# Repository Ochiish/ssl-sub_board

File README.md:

# SubBoard for SSL

## Overview

This is a sub-board installed in the SSL robot.
The boost circuit, neopixel, phototransistor, etc. are controlled by stm32, and CAN communication is performed with the main board.

## Requirement

- KiCad 7.0.5

## Usage

Good luck...

## Features

This is a sub-board installed in an SSL robot. The board is equipped with various components such as a boost circuit, NeoPixels, phototransistors, etc., all controlled by an STM32 microcontroller. 

- This microcontroller offers advanced programming and processing capabilities, efficiently managing the robot's diverse functions.

- The boost circuit optimizes power supply, ensuring each component on the board operates at the correct voltage. It elevates the low voltage from the battery, distributing power as needed.

- NeoPixels are individually controllable LEDs used for visual feedback and status indication on the robot. These LEDs can be customized in color and brightness through programming, intuitively conveying the robot's status to the operator.

- Phototransistors detect light intensity and convert this information into digital signals. This is a crucial sensor for environmental awareness and obstacle detection in the robot.

- Furthermore, this robot is equipped with a thermistor for measuring the temperature of the solenoid coil. The thermistor plays a vital role in monitoring the heat generated by the solenoid, preventing overheating and enhancing the robot's safety and equipment lifespan.

- Additionally, the sub-board incorporates protective circuits around the power supply, safeguarding it against overvoltage and short circuits. 

- These circuits are essential for maintaining power stability while minimizing electrical risks.

- The sub-board communicates with the main board using the CAN communication protocol. CAN communication is known for its high reliability and error detection capabilities, ensuring secure data exchange between different parts of the robot. This allows for smooth overall operation and the ability to perform more complex tasks.

In this way, the sub-board supports crucial functions of the SSL robot, drawing out the robot's maximum performance through advanced technology and meticulous design.

## Reference

https://www.analog.com/media/jp/technical-documentation/data-sheets/j3751fc.pdf

## Author

[@Allsatako](http://twitter.com/Allsatako)

mail to: rionesslq@gmail.com

## Licence

There is no license as this is open source hardware.

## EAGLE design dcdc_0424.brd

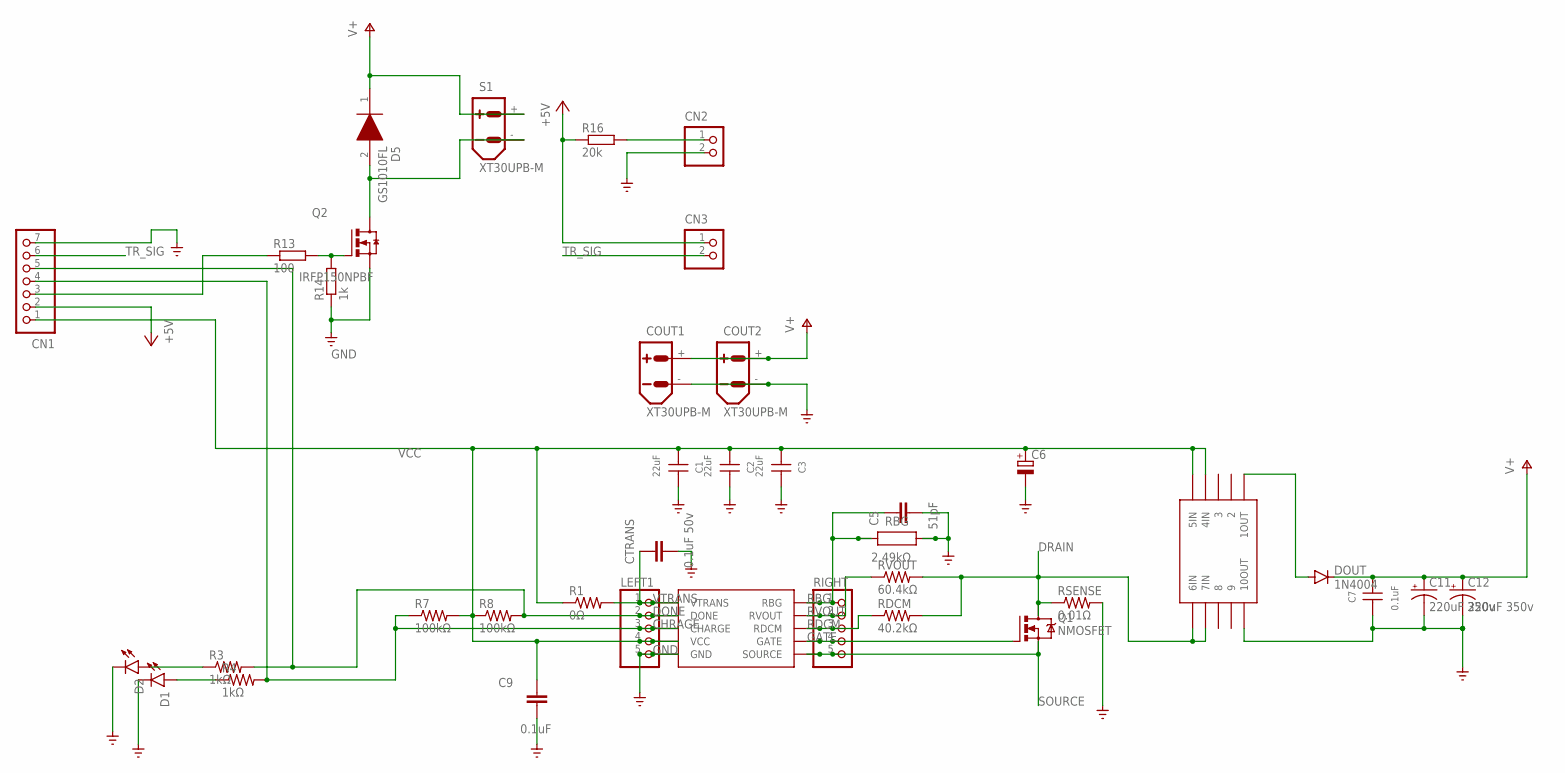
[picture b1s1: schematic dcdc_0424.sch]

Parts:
C1, C2, C3: 22uF; WCAP-CSGP_1210_H0.95
C5: 51pF; CAP_0603
C6: CPOL-EUTT2D6; TT2D6
C7: 0.1uF; WCAP-CSGP_1812_H1.25
C9: 0.1uF; CAP_0603
C11, C12: 220uF 350v; E7,5-18
CN1: B7B-XH-A
CN2, CN3: B2B-XH-A
COUT1, COUT2: XT30UPB-M
CTRANS: 0.1uF 50v; CAP_1206
D1, D2: LED_RADIALWHITE; LEDRD254W60D565H860B_W
D5: GS1010FL; SODFL3618X110N
DOUT: 1N4004; DO41-10
LEFT1: PINHD-1X5; 1X05
Q1: NMOSFET; TO220BV
Q2: IRFP150NPBF; TO-247AC
R1: 0Ω; M2012
R3, R4: 1kΩ; RES_0402
R7, R8: 100kΩ; R1210
R13: 100; R0603
R14: 1k; R0603
R16: 20k; R0603
RBG: 2.49kΩ; WRIS_PSMC_2512_6.3X3.1X0.51X1.1(LXWXHXPW)
RDCM: 40.2kΩ; RES_0805
RIGHT: PINHD-1X5; 1X05
RSENSE: 0.01Ω; RES_1206
RVOUT: 60.4kΩ; RES_0805
S1: XT30UPB-M
U$1: LT3750_2
U$2: 32052

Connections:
2: D5.2 (A), Q2.D, S1.-
+5V: CN1.2, CN3.1, R16.1
CHRAGE: CN1.4, LEFT1.3, R4.2, R7.1, U$1.CHARGE
DONE: CN1.5, LEFT1.2, R3.2, R8.2, U$1.DONE
DRAIN: Q1.D, RDCM.2, RSENSE.1, RVOUT.2, U$2.6IN, U$2.7IN
GATE: Q1.G, RIGHT.4, U$1.GATE
GND: C1.2, C2.2, C3.2, C5.2, C6.-, C7.1, C9.2, C11.-, C12.-, CN1.7, CN2.2, COUT1.-, COUT2.-, CTRANS.2, D1.C, D2.C, LEFT1.5, Q2.S, R14.1, RBG.2, RSENSE.2, U$1.GND, U$2.10OUT
unnamed: CN1.3, R13.1
unnamed: DOUT.A, U$2.1OUT
unnamed: D1.A, R4.1
unnamed: D2.A, R3.1
unnamed: Q2.G, R13.2, R14.2
unnamed: CN2.1, R16.2
RBG: C5.1, RBG.1, RIGHT.1, U$1.RBG
RDCM: RDCM.1, RIGHT.3, U$1.RDCM
RVOUT: RIGHT.2, RVOUT.1, U$1.RVOUT
SOURCE: Q1.S, RIGHT.5, U$1.SOURCE
TR_SIG: CN1.6, CN3.2
V+: C7.2, C11.+, C12.+, COUT1.+, COUT2.+, D5.1 (K), DOUT.C, S1.+
VCC: C1.1, C2.1, C3.1, C6.+, C9.1, CN1.1, LEFT1.4, R1.1, R7.2, R8.1, U$1.VCC, U$2.4IN, U$2.5IN
VTRANS: CTRANS.1, LEFT1.1, R1.2, U$1.VTRANS

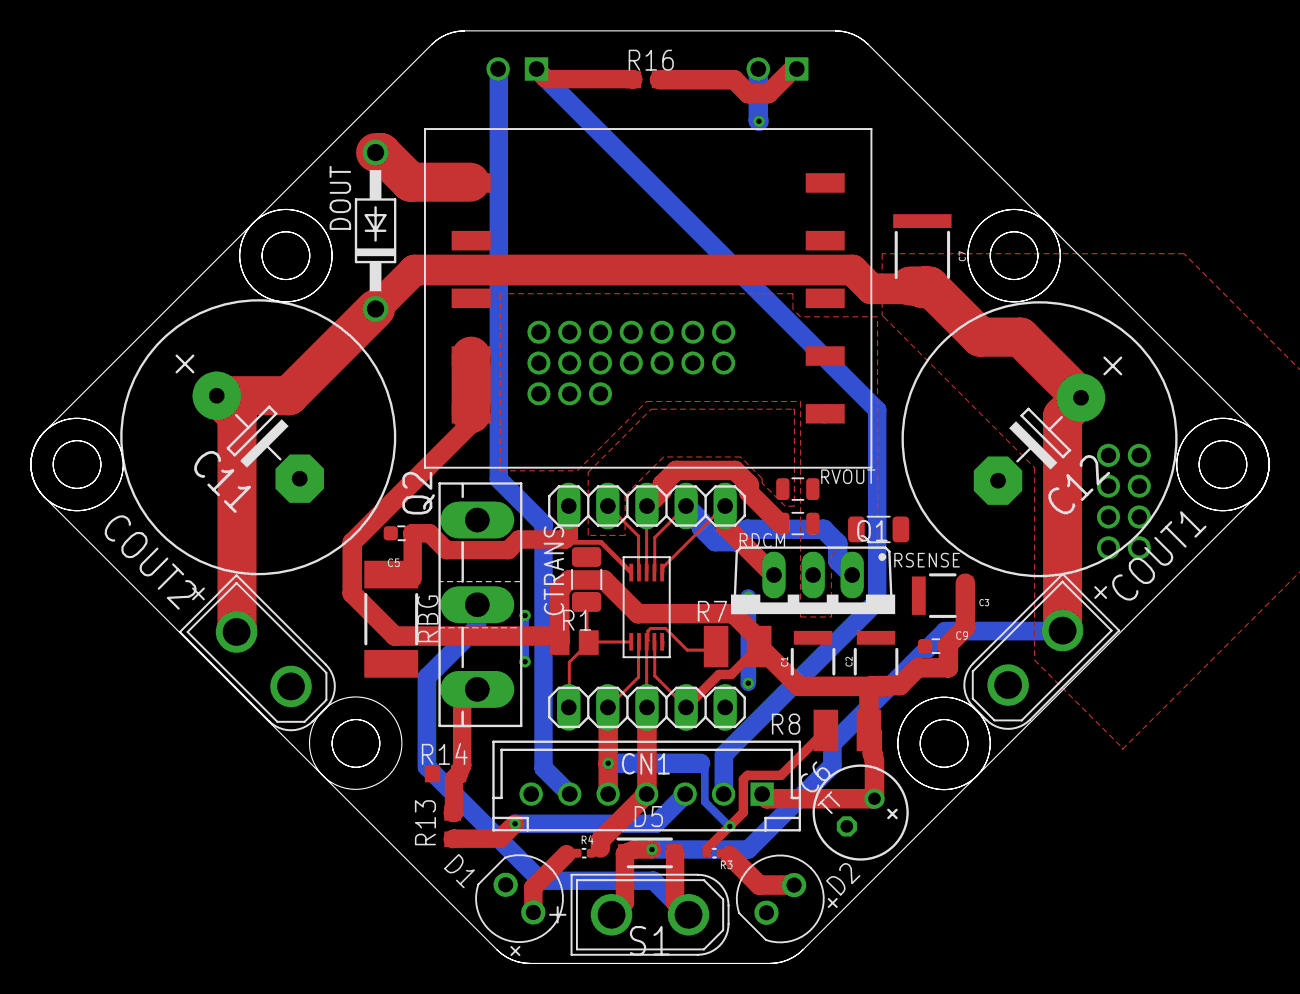
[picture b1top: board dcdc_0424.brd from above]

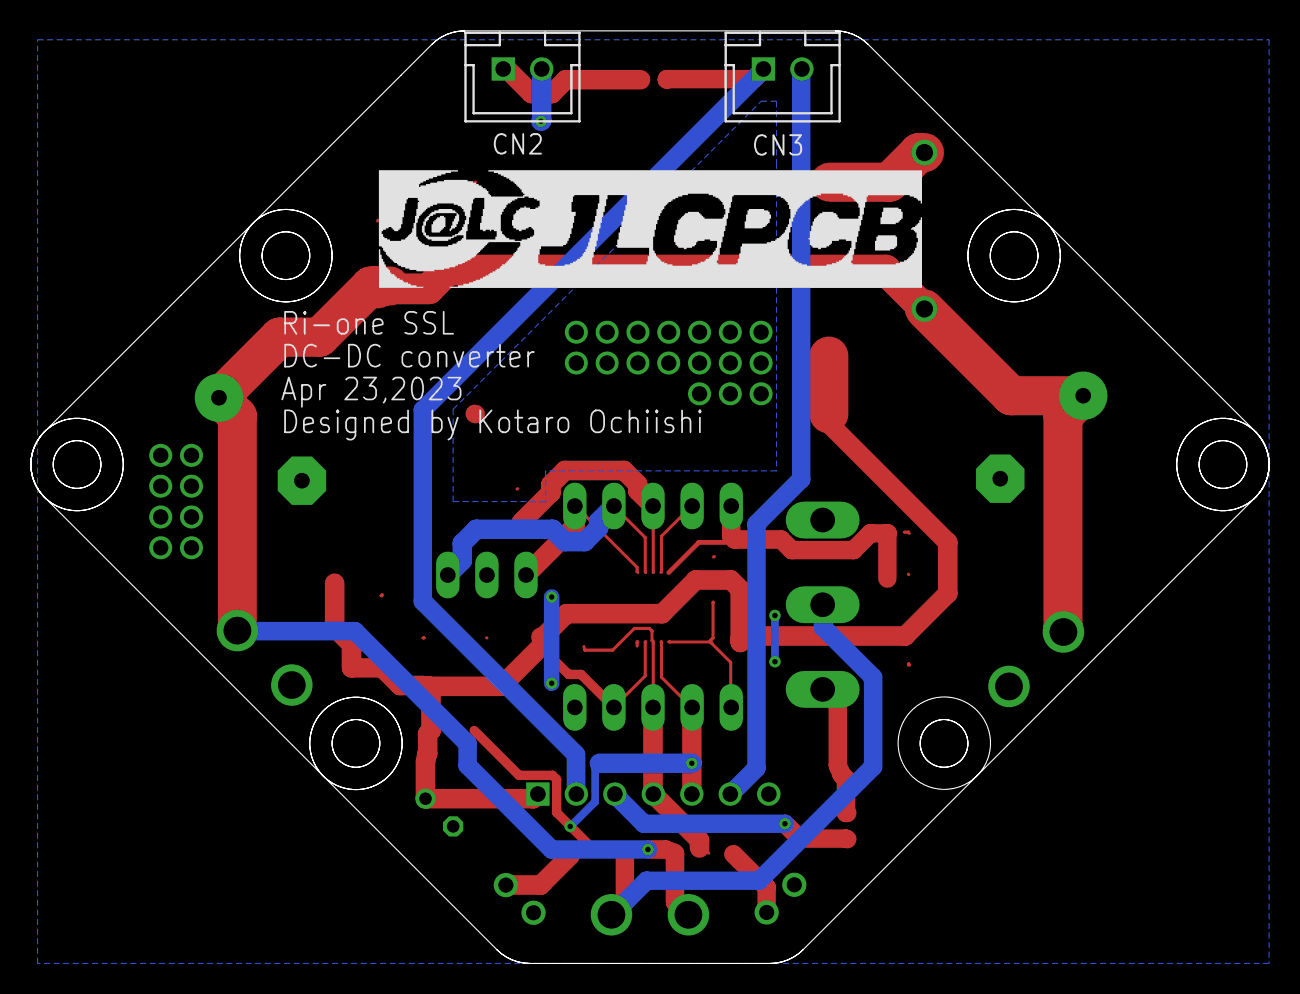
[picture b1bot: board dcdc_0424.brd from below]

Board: 2 copper layers, 80.4 x 60.6 mm, 38 parts (2 on the bottom side), 21 nets.

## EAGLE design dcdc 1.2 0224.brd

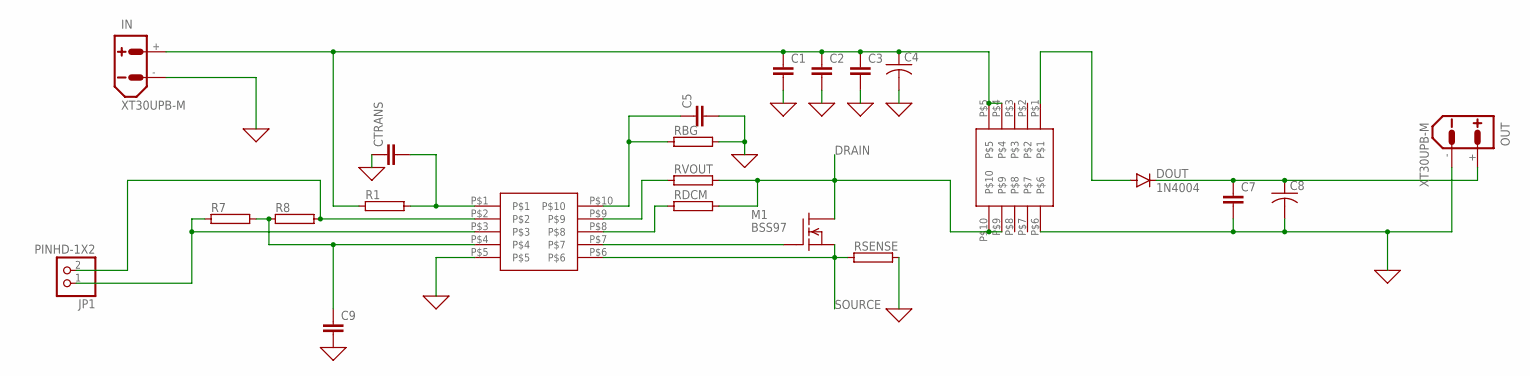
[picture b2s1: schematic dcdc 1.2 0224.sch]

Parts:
C1, C2, C3, C5, C7, C9: C5/3.5; C5B3.5
C4, C8: C-US050-050X075; C050-050X075
CTRANS: C5/3.5; C5B3.5
DOUT: 1N4004; DO41-10
IN: XT30UPB-M
JP1: PINHD-1X2; 1X02
M1: BSS97; TO202
OUT: XT30UPB-M
R1, R7, R8: RAC01; AC01
RBG: RAC01; AC01
RDCM: RAC01; AC01
RSENSE: RAC01; AC01
RVOUT: RAC01; AC01
U$1: LT3750
U$2: 32052

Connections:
0: C1.2, C2.2, C3.2, C4.2, C5.2, C7.2, C8.2, C9.2, CTRANS.1, IN.-, OUT.-, RBG.2, RSENSE.2, U$1.P$5, U$2.P$6
DRAIN: M1.2 (D), RDCM.2, RVOUT.2, U$2.P$9, U$2.P$10
unnamed: C9.1, R7.2, R8.1, U$1.P$4
unnamed: C5.1, RBG.1, U$1.P$10
unnamed: RVOUT.1, U$1.P$9
unnamed: RDCM.1, U$1.P$8
unnamed: JP1.1, R7.1, U$1.P$3
unnamed: M1.3 (G), U$1.P$7
unnamed: DOUT.A, U$2.P$1
unnamed: JP1.2, R8.2, U$1.P$2
unnamed: C7.1, C8.1, DOUT.C, OUT.+
unnamed: C1.1, C2.1, C3.1, C4.1, IN.+, R1.1, U$2.P$4, U$2.P$5
unnamed: CTRANS.2, R1.2, U$1.P$1
SOURCE: M1.1 (S), RSENSE.1, U$1.P$6

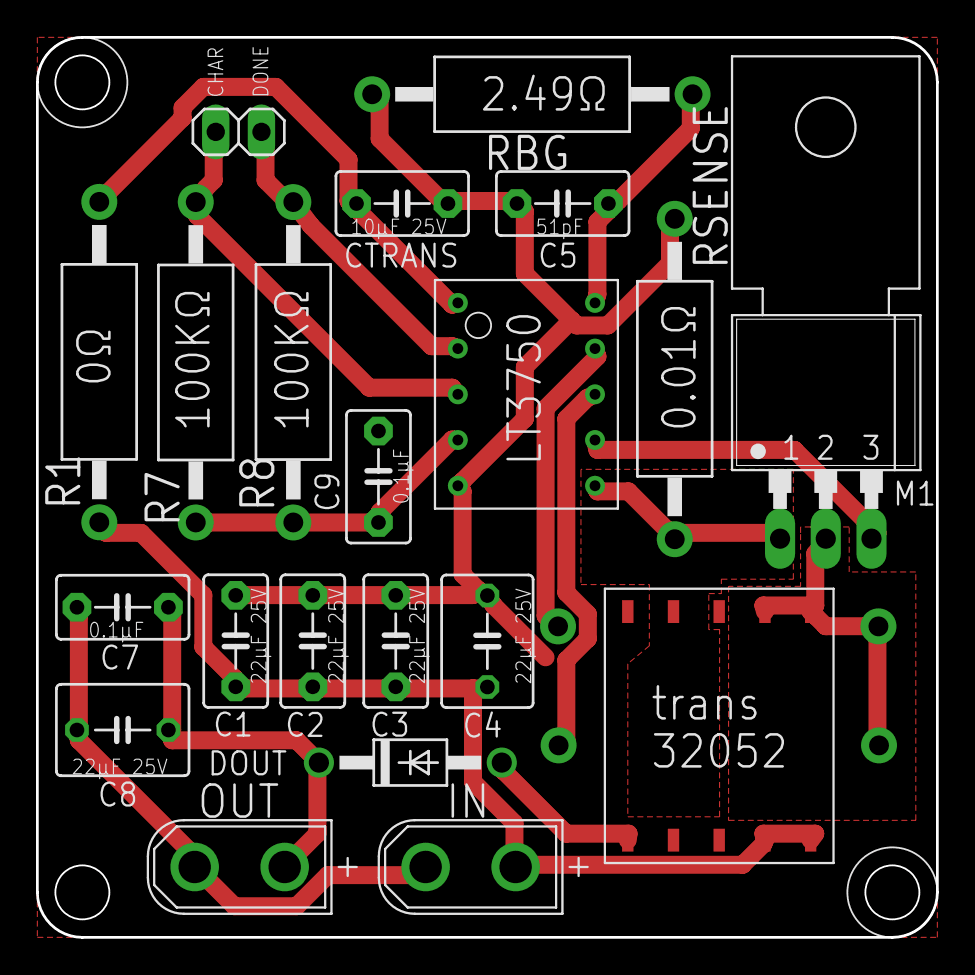
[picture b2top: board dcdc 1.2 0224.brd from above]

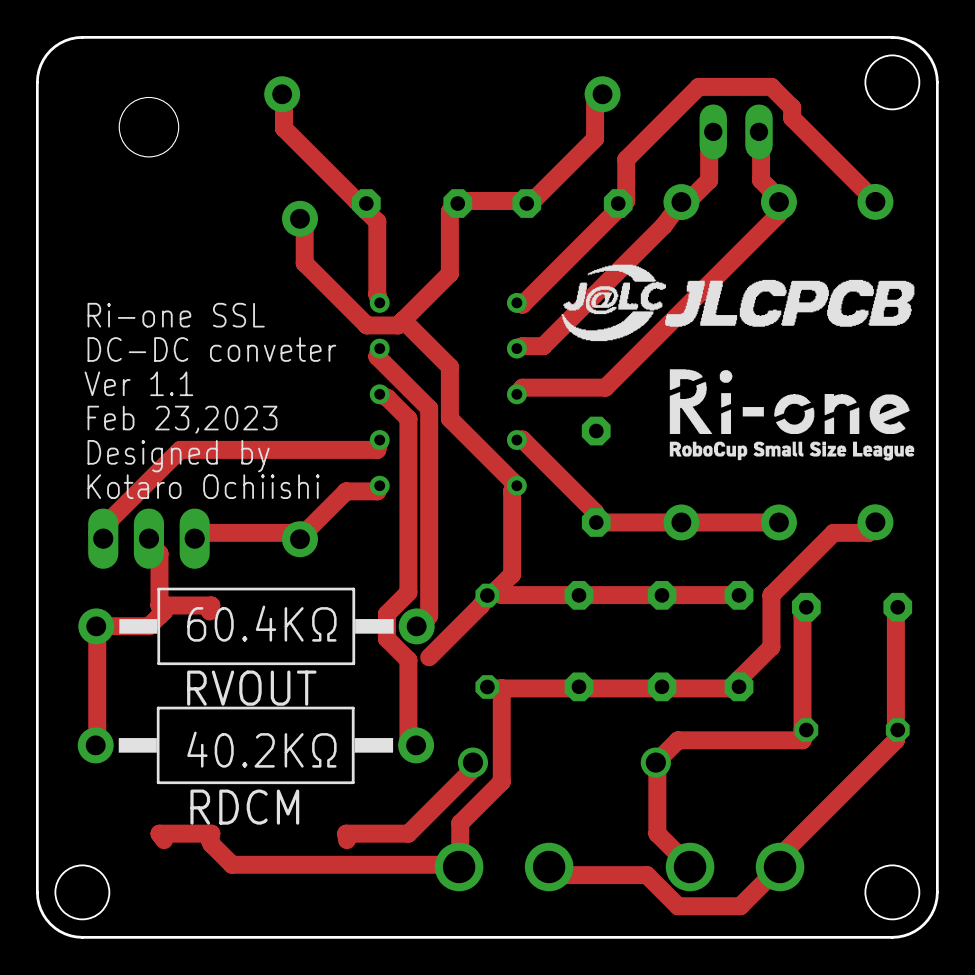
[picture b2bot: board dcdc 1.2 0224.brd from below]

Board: 4 copper layers, 50.0 x 50.0 mm, 23 parts (2 on the bottom side), 14 nets.

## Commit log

2023-02-23 second commit
2023-02-24 third commit
2023-03-04 commit4
2023-03-04 commit6
2023-04-21 test0422
2023-05-24 Add files via upload
    designed with kicad
2023-06-27 last circuit
2023-11-29 add .gitignore
2023-11-29 add imagefile
2023-11-29 add newimage

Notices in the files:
parts and their libraries:
Wurth_Capacitors_WCAP-CSGP: Copyright: Würth Elektronik
